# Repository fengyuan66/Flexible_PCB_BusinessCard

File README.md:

# Flexible PCB card
A PCB business card inspired by Github's, with displays that can adapt to whichever event I attend

**Notes**

I've included the firmware. However, it hasn't gone through any testing yet. I've tried my best to understand and check that the code reflect the irl board. Please see  journal for more details regarding the making of the firmware.

Also, I know that the PCB business card is now 2 points, but I genuinely feel like that this design deserves at least fits in the 4 point category for its features. Unlike some of my other projects, I am pretty confident in my judgement for this one. Though if it doesn't deserve 4 points, I'm okay with that as well.

<h3>Project Description</h3>

This is a PCB business card with my basic contact info printed on it. It is based off this really cool PCB business card design on Github (I couldn't find the original link :() (Hi this is Harry from like 1 hour later, turns out it's the "Github Universe Badge" as pointed out by this one guy's journal). Its main feature is its ability to display different things under different contexts. The way it works is simple...

1. There exists an image and a text folder in an external micro SD card
2. Files are stored accordingly into the external micro SD card's folders
3. The displays iterate through the contents in their corresponding folder when their corresponding button is pressed

There's also some cool LED lights to light up the hole thing and grant aura to the otherwise bland-looking information silkscreen. You can toggle them with its own button, too!

The top square display is for images, the bottom is for texts.

<h3>Why I built it</h3>

To be blatantly honest...

**1. To get enough points and get reimbursement my flight**

I feel kinda upset because the price of my flight dropped by like 300 dollars days after I bought it. Also I'm like 2 points away from getting the reimbursement to completely cover my flight...

But at the same time...

**2. It's something that's useful**

A regular PCB business card I find is too generic. A common need I find when attending events is that I sometimes need to display some sort of information. This could look like a QR code when running the next boba drops workshop, or displaying which school you are from during a field trip. Having a PCB card that can display information that can change depending on the event is super helpful because not only does it make you not have to hold up a piece of paper, people would pay more attention at the displayed information because they find it cool.

**2. Unique technical skills involved**

My previous project taught me how to (in an introductory manner) use Kicad's schematic tool and Fusion360's modelling. This project completes the Kicad design process by involving uniquely PCB design and firmware. I think that with these two Highway projects, I would have an introduction to the whole hardware design process.

<h3>Pictures of my project</h3>

<h2>Full 3D model</h2>

PCB Card - no displays + microcontroller

PCB Card - with displays + microcontroller (and yes the 1.8"OLED and SD card receptor looks weird but trust me it's wired correctly in that way)

<h2>Schematics<h2>

**LEGEND:**

Blue = controls

Yellow = grounds

Green = power

<h2>BOM</h2>

By the way, the JLPCB quote I couldn't include a link to, so here's an image instead:

| Platform | Description                            | Price per listed lot | # of parts per listed lot | Lots purchased    | Final price (+shipping), (CAD) | Final price (USD) | Already owned? | Comments                                                                                                      | Link                                                                                                                                                                                                                                                                                                                                                                                                                                                                                                                                                                                                                                  |
|----------|----------------------------------------|----------------------|---------------------------|-------------------|--------------------------------|-------------------|----------------|---------------------------------------------------------------------------------------------------------------|---------------------------------------------------------------------------------------------------------------------------------------------------------------------------------------------------------------------------------------------------------------------------------------------------------------------------------------------------------------------------------------------------------------------------------------------------------------------------------------------------------------------------------------------------------------------------------------------------------------------------------------|
| Taobao   | WS2812 LED light strip                 | 0.19                 | 1                         | 1                 | 0.19                           | 0.1387            | No             |                                                                                                               | https://item.taobao.com/item.htm?abbucket=8&id=713275663555&ltk2=1753504932468kc5d1mva35jqm2i7ez5niq&ns=1&priceTId=213e03b917535049057584274e1bd4&skuId=5162177838989&spm=a21n57.1.hoverItem.32&utparam=%7B%22aplus_abtest%22%3A%22ddbe73aa2c41ad0c6b1321407c129fc9%22%7D&xxc=taobaoSearch                                                                                                                                                                                                                                                                                                                                            |
| Taobao   | MicroSD card interface                 | 0.74                 | 1                         | 1                 | 0.74                           | 0.5402            | No             |                                                                                                               | https://detail.tmall.com/item.htm?from=cart&id=41337396998&pisk=gUnKXfaxSCA3spnLIv8GEGrEO1vi9FDEBXkfq7VhPfhtNbelqYNu2bh-wW4WTkm-6bG8EgDSq8i8Yc0hqWAU2YG02IADmnDELkrWiIm7TFp8c-w5R_4CChZuevq5H5kELuP5I_Tm5vWJ0VGFN8NWBlw83aZ5R8_6B82uNuNQP1__h5Z7VzNC1Ow3H9s7NM9TC82PA6NCRNt_KJZ7NbZWBANaeuNSMpTLZCVV22EQeYQPf8j5VceL5nDQ13ksbJF0ividVg9zpyFjd5dCuorQ5Yz-4TS8lvgqa-GCOQFrXAiIljOG-WgYex0-dHs_xDkIlziXaaGYvbUjAPB5AlZ__lescLb4scFnNDU6niUufm4bAVYwtzqLHbiE9TISGADmYPoJM1Nr--r_e0Jfy7U54onmDK2liSelRdpOzazQQV9SslD-T5oTBSvMIa7zWXeTidpOzazQQRFDQf7PzPhd.&skuId=5051669025377&spm=a1z0d.6639537%2F202410.item.d41337396998.174b7484ndtpOq |
| Taobao   | 0.91 inch OLED display (text)          | 1.12                 | 1                         | 1                 | 1.12                           | 0.8176            | No             |                                                                                                               | https://detail.tmall.com/item.htm?abbucket=8&id=600261313078&ltk2=1753504398479ci2khaq2kqmhe2vs5xy105&ns=1&priceTId=215042e817535043927425208e1a9d&skuId=4193259944122&spm=a21n57.1.hoverItem.2&utparam=%7B%22aplus_abtest%22%3A%22d5c49652632f13f333e3844f6e84d441%22%7D&xxc=taobaoSearch                                                                                                                                                                                                                                                                                                                                            |
| Taobao   | 1.8 inch OLED display (image)          | 2.06                 | 1                         | 1                 | 2.06                           | 1.5038            | No             |                                                                                                               | https://item.taobao.com/item.htm?abbucket=8&id=866673025601&ltk2=1753504364623ep1jt9x19yg84l7wt4ls&ns=1&priceTId=2150470017535043573542103e0ef5&skuId=5691733032070&spm=a21n57.1.hoverItem.2&utparam=%7B%22aplus_abtest%22%3A%22499fcad78ff98e920f8aab6d2d4fccf8%22%7D&xxc=taobaoSearch                                                                                                                                                                                                                                                                                                                                               |
| Taobao   | Small push buttons                     | 0.37                 | 20                        | 1                 | 0.37                           | 0.2701            | No             |                                                                                                               | https://detail.tmall.com/item.htm?abbucket=8&id=558374381395&ltk2=1753504272981kvblexa4kwl1wy69p4990u&ns=1&skuId=3471184705960&spm=a21n57.1.hoverItem.2&utparam=%7B%22aplus_abtest%22%3A%227af594b2bd48a0bd27b0f88fe3ede619%22%7D&xxc=taobaoSearch                                                                                                                                                                                                                                                                                                                                                                                    |
| Taobao   | Resistors (330 ohms)                   | 0.36                 | 100 (supposedly)          | 1                 | 0.36                           | 0.2628            | No             | I don't have access in China                                                                                  | https://detail.tmall.com/item.htm?abbucket=8&id=604722661912&ltk2=175350212768347o5euee9doqh9nbgmakur&ns=1&skuId=4405819222938&spm=a21n57.1.hoverItem.5&utparam=%7B%22aplus_abtest%22%3A%22dba4d2246491f2dd2822195b487cf587%22%7D&xxc=taobaoSearch                                                                                                                                                                                                                                                                                                                                                                                    |
| Taobao   | Resistors (47k ohms)                   | 0.36                 | 100 (supposedly)          | 1                 | 0.36                           | 0.2628            | No             | I don't have access in China                                                                                  | https://detail.tmall.com/item.htm?abbucket=8&id=604943038864&ltk2=1753502399979i3pfv8tp7etgh8v9tofn&ns=1&priceTId=215044cc17535018153884876e0ecd&skuId=4235104924044&spm=a21n57.1.hoverItem.1&utparam=%7B%22aplus_abtest%22%3A%2255916e9cfae7a6eee227c2700b316cce%22%7D&xxc=taobaoSearch                                                                                                                                                                                                                                                                                                                                              |
| Taobao   | 512mb MicroSD card + card reader (pack)  | 1.53                 | 1 of each                 | 1                 | 1.53                           | 1.1169            | No             | The reason for the SD card addon option is because I don't have means to write in the card right now in China | https://detail.tmall.com/item.htm?detail_redpacket_pop=true&id=648801516814&ltk2=1753502455647mv98w41yr72et30952i8c&ns=1&priceTId=2147821617535024397927885e18bb&query=%E8%BF%B7%E4%BD%A0SD%E5%8D%A1&skuId=4760055037612&spm=a21n57.1.hoverItem.1&utparam=%7B%22aplus_abtest%22%3A%22d4e84d49866cf6c5d3cc5f9e572d732d%22%7D&xxc=ad_ztc                                                                                                                                                                                                                                                                                                |
| Taobao   | Raspberry Pi Pico w/ pins (Type-C USB) | 9.23                 | 1                         | 1                 | 9.23                           | 6.7379            | No             |                                                                                                               | https://item.taobao.com/item.htm?abbucket=8&id=637653493419&ltk2=1753505064511vsrzv28u4lqitn0uoeoxxq&ns=1&priceTId=215041fb17535050508425643e1ae8&skuId=5953375371936&spm=a21n57.1.hoverItem.3&utparam=%7B%22aplus_abtest%22%3A%227d3fbc0a71df18f4cce1fbea7a63f8af%22%7D&xxc=taobaoSearch                                                                                                                                                                                                                                                                                                                                             |
| JLPCB    | PCB board                              | 2.72                 | 5 (can't change to lower) | 1                 | 3.72                           | 2.7156            | No             |  + 3.72 shipping, -2.72 coupon. Can't add link so image instead.                                              |                                                                                                                                                                                                                                                                                                                                                                                                                                                                                                                                                                                                                                       |
|          |                                        |                      |                           |                   |                                |                   |                |                                                                                                               |                                                                                                                                                                                                                                                                                                                                                                                                                                                                                                                                                                                                                                       |
|          |                                        |                      |                           | Total (CAD, USD): | 19.68                          | 14.3664           |                |                                                                                                               |                                                                                                                                                                                                                                                                                                                                                                                                                                                                                                                                                                                                                                       |

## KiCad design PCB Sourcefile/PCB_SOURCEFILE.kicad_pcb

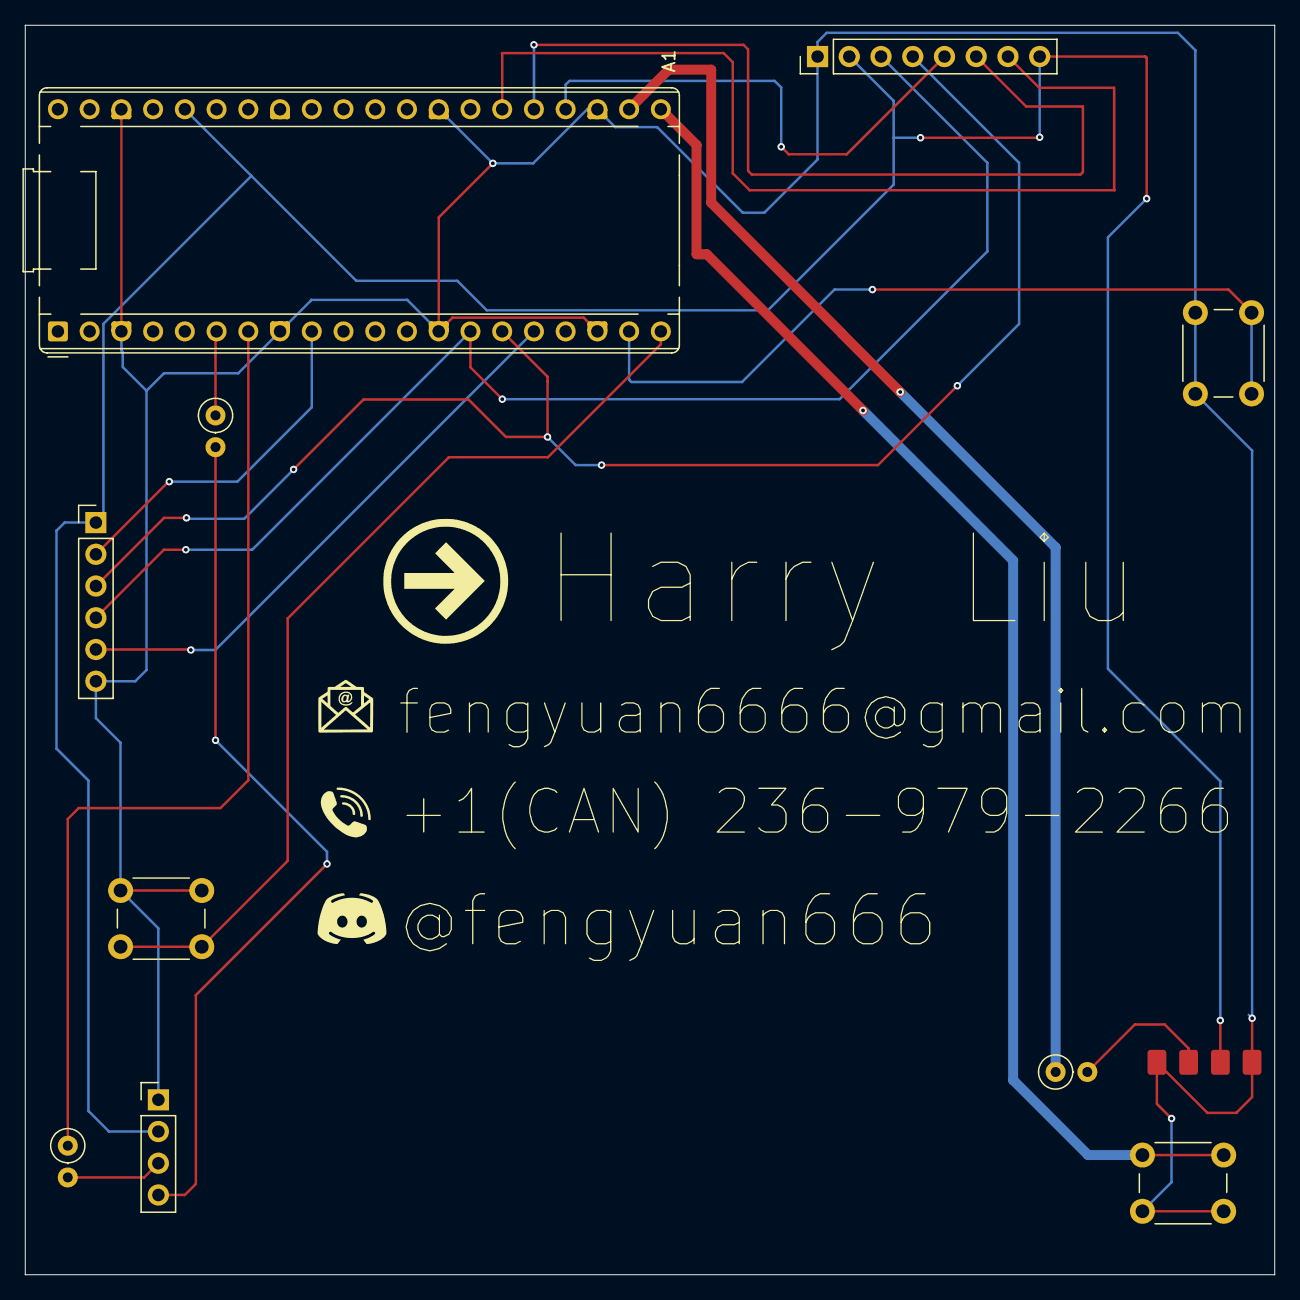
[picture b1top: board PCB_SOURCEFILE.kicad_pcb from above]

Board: 2 copper layers, 100.0 x 100.0 mm, 11 parts (0 on the bottom side), 18 nets.

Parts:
47kOhms1, 47kOhms2, 330Ohms1: R; R_Axial_DIN0207_L6.3mm_D2.5mm_P2.54mm_Vertical
A1: RaspberryPi_Pico; RaspberryPi_Pico_Common_THT
J1: Conn_01x04; PinHeader_1x04_P2.54mm_Vertical
J2: Conn_01x08; PinHeader_1x08_P2.54mm_Vertical
J3: Conn_01x06; PinHeader_1x06_P2.54mm_Vertical
J4: Conn_01x04; LED_Strip1x04
LED_Buttons1: SW_Push; SW_PUSH_6mm
OLEDscreenbutton1: SW_Push; SW_PUSH_6mm
TextScreenButton1: SW_Push; SW_PUSH_6mm

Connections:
unnamed: A1.36 (3V3), J1.2, J2.2, J2.8, J3.1, J4.3
unnamed: 47kOhms2.1, A1.6 (GPIO4)
unnamed: 47kOhms1.1, A1.7 (GPIO5)
unnamed: A1.9 (GPIO6), J3.2
unnamed: A1.14 (GPIO10), J2.3, J3.4
unnamed: A1.15 (GPIO11), J2.4, J3.3
unnamed: A1.16 (GPIO12), J3.5
unnamed: A1.19 (GPIO14), OLEDscreenbutton1.2
unnamed: A1.20 (GPIO15), TextScreenButton1.2
unnamed: A1.21 (GPIO16), LED_Buttons1.1
unnamed: 330Ohms1.1, A1.22 (GPIO17)
unnamed: A1.24 (GPIO18), J2.5
unnamed: A1.25 (GPIO19), J2.6
unnamed: A1.26 (GPIO20), J2.7
unnamed: A1.3 (GND), A1.8 (GND), A1.13 (GND), A1.18 (GND), A1.23 (GND), A1.28 (GND), A1.38 (GND), J1.1, J2.1, J3.6, J4.1, J4.4, LED_Buttons1.2, OLEDscreenbutton1.1, TextScreenButton1.1
unnamed: 47kOhms1.2, J1.3
unnamed: 47kOhms2.2, J1.4
unnamed: 330Ohms1.2, J4.2

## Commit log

2025-07-06 Initialise
2025-07-07 2025-07-06 journal update
2025-07-09 Update journal + upload README V1
2025-07-09 Fix: Increase spacing between lines for schematic legend
2025-07-09 Format readme
2025-07-09 Fix h2 tag endings
2025-07-09 Add total time
2025-07-09 Clean up all images to /Assets
2025-07-09 Fix BOM
2025-07-09 Fix schematics (erase "-1")
2025-07-09 Add PCB sourcefile
2025-07-09 Fix firmware (it's C++ now + the previous one was empty)
2025-07-09 Add disclaimer that it's not actually micropython
2025-07-09 I finally found what the name is
2025-07-09 Add firmware disclaimer
2025-07-09 Add 4 point disclaimer
2025-07-25 Make PCB 100mmx100mm
2025-07-26 Update README images
2025-07-26 Update files in root, update BOM in readme
2025-07-26 Its a 512mb card, not a 1 gb
2025-07-26 Update journal + time
2025-07-26 Add text to the with components board
